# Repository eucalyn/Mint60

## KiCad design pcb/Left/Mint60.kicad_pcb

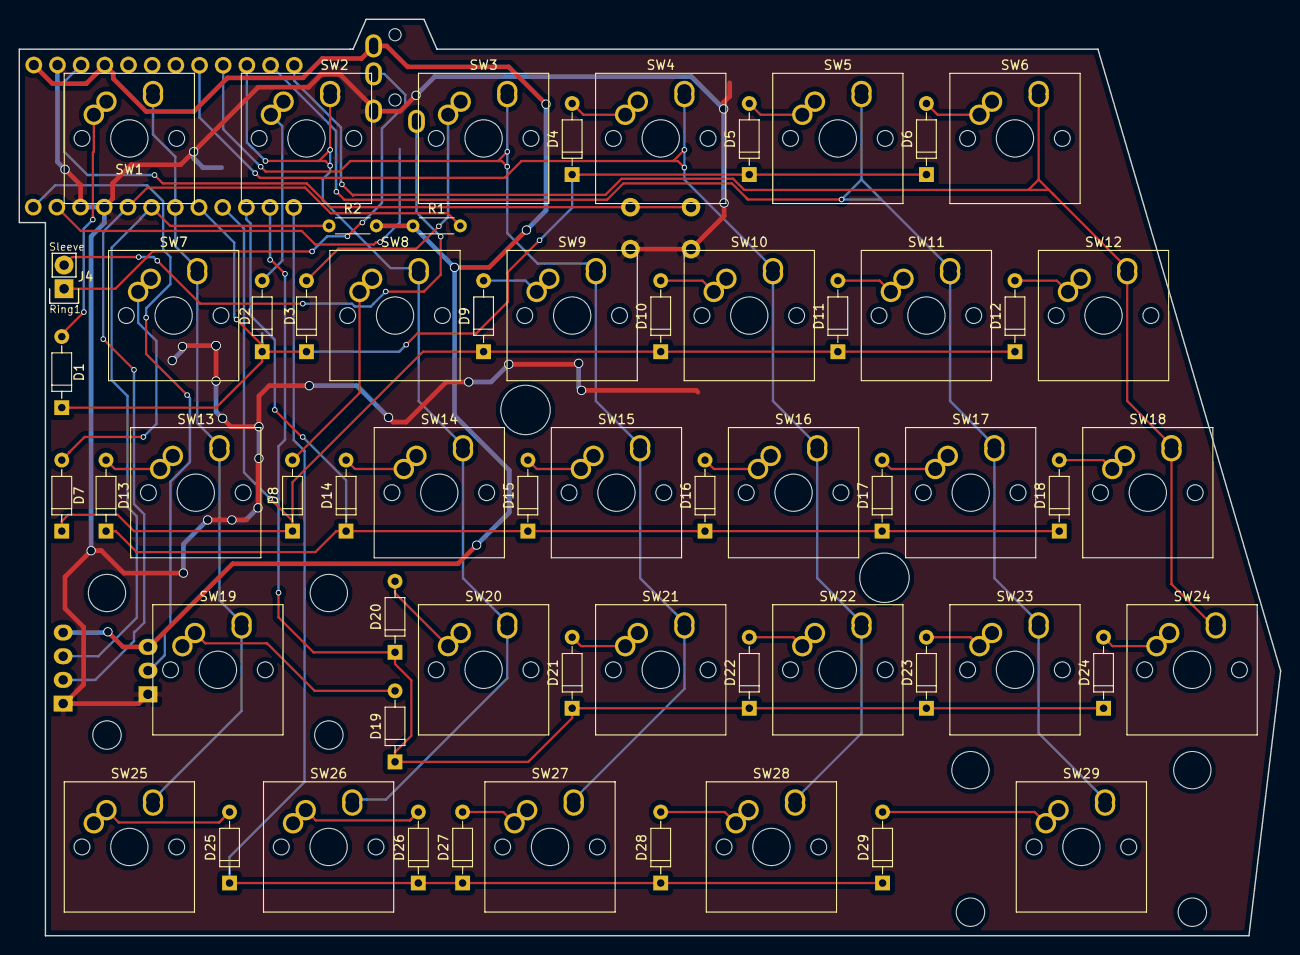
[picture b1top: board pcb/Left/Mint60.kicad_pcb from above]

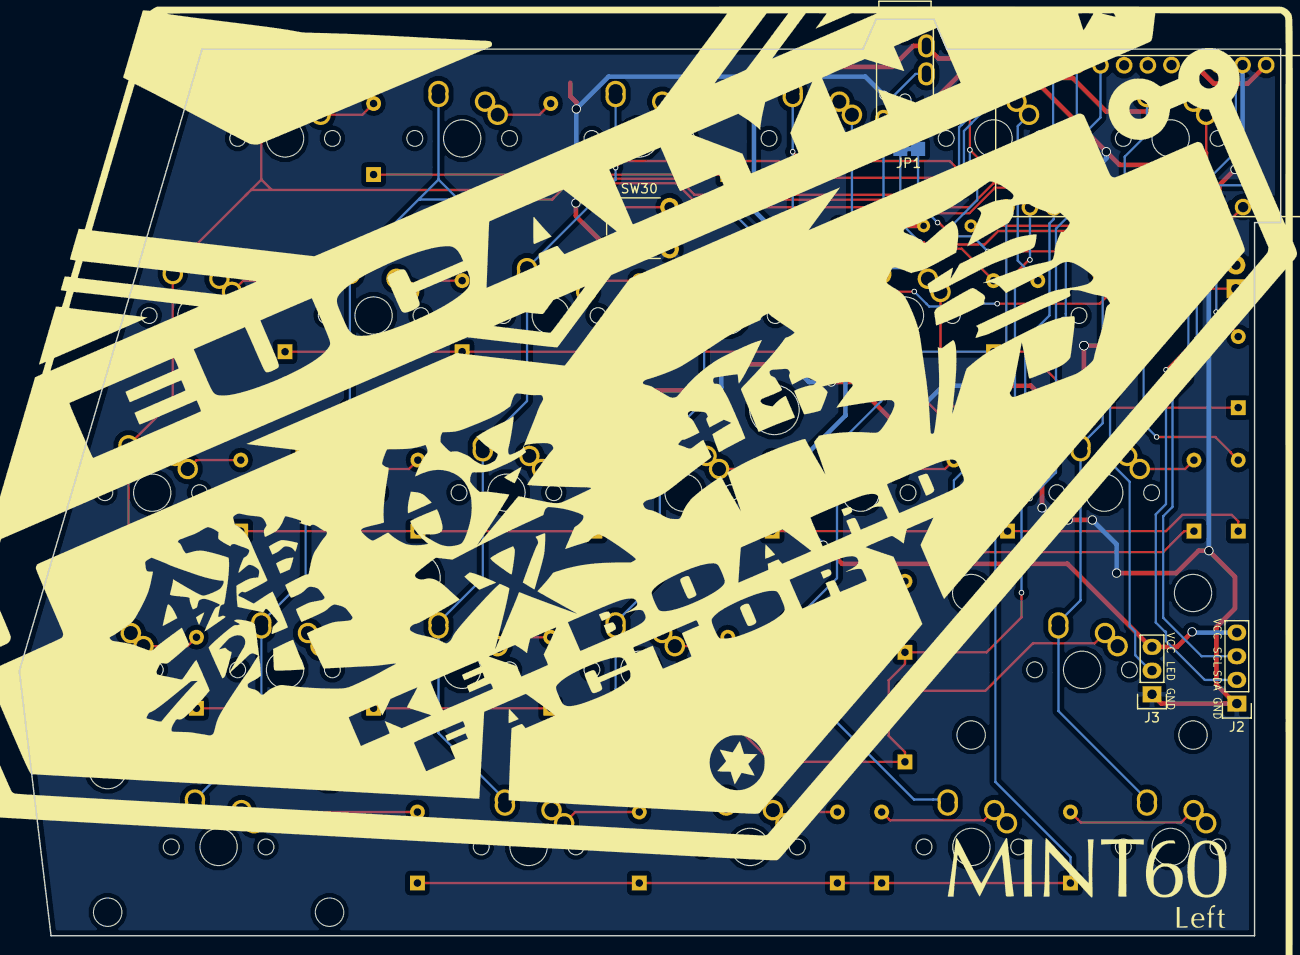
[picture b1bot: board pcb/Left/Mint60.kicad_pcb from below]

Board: 2 copper layers, 135.3 x 98.3 mm, 67 parts (5 on the bottom side), 49 nets.

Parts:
D1, D2, D3, D4, D5, D6, D7, D8, D9, D10, D11, D12, D13, D14, D15, D16, D17, D18, D19, D20, D21, D22, D23, D24, D25, D26, D27, D28, D29: D; Diode
J1: MJ-4PP-9; TRRS_JACK_MJ4PP9_fr
J2: Conn_01x04; Pin_Header_Straight_1x04
J3: Conn_01x03; Pin_Header_Straight_1x03
J4: Conn_01x02; Pin_Header_Straight_1x02
JP1: Jumper_NC_Small; JumperClose
R1, R2: R; R_Axial_DIN0204_L3.6mm_D1.6mm_P5.08mm_Horizontal
SW1, SW2, SW3, SW4, SW5, SW6, SW7, SW8, SW9, SW10, SW11, SW12, SW13, SW14, SW15, SW16, SW17, SW18, SW20, SW21, SW22, SW23, SW24, SW25, SW26, SW27, SW28: SW_Push; SW_Cherry_Matias_1.00u_PCB
SW19, SW29: SW_Push; SW_Cherry_Matias_2.00u_PCB-flip
SW30: SW_Push; SW_PUSH_6mm
U1: ProMicro; ProMicro-Flip

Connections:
+5V: J1.3, J2.4, J3.3, R1.1, R2.2, U1.21, U1.24
Col0: SW1.1, SW7.1, SW13.1, SW19.1, SW25.1, U1.7
Col1: SW2.1, SW8.1, SW14.1, SW20.1, SW26.1, U1.15
Col2: SW3.1, SW9.1, SW15.1, SW21.1, SW27.1, U1.16
Col3: SW4.1, SW10.1, SW16.1, SW22.1, SW28.1, U1.17
Col4: SW5.1, SW11.1, SW17.1, SW23.1, SW29.1, U1.14
Col5: SW6.1, SW12.1, SW18.1, SW24.1, U1.13
Data: JP1.1, U1.2
GND: J1.1, J2.1, J3.1, SW30.2, U1.3, U1.4, U1.23
LED: J3.2, U1.1
unnamed: D1.2, SW1.2
unnamed: D2.2, SW2.2
unnamed: D3.2, SW3.2
unnamed: D4.2, SW4.2
unnamed: D5.2, SW5.2
unnamed: D6.2, SW6.2
unnamed: D7.2, SW7.2
unnamed: D8.2, SW8.2
unnamed: D9.2, SW9.2
unnamed: D10.2, SW10.2
unnamed: D11.2, SW11.2
unnamed: D12.2, SW12.2
unnamed: D13.2, SW13.2
unnamed: D14.2, SW14.2
unnamed: D15.2, SW15.2
unnamed: D16.2, SW16.2
unnamed: D17.2, SW17.2
unnamed: D18.2, SW18.2
unnamed: D19.2, SW19.2
unnamed: D20.2, SW20.2
unnamed: D21.2, SW21.2
unnamed: D22.2, SW22.2
unnamed: D23.2, SW23.2
unnamed: D24.2, SW24.2
unnamed: D25.2, SW25.2
unnamed: D26.2, SW26.2
unnamed: D27.2, SW27.2
unnamed: D28.2, SW28.2
unnamed: D29.2, SW29.2
unnamed: J1.2, J4.1, JP1.2
unnamed: J1.4, J4.2
Reset: SW30.1, U1.22
Row0: D1.1, D2.1, D3.1, D4.1, D5.1, D6.1, U1.8
Row1: D7.1, D8.1, D9.1, D10.1, D11.1, D12.1, U1.9
Row2: D13.1, D14.1, D15.1, D16.1, D17.1, D18.1, U1.10
Row3: D19.1, D20.1, D21.1, D22.1, D23.1, D24.1, U1.11
Row4: D25.1, D26.1, D27.1, D28.1, D29.1, U1.12
SCL: J2.3, R2.1, U1.6
SDA: J2.2, R1.2, U1.5

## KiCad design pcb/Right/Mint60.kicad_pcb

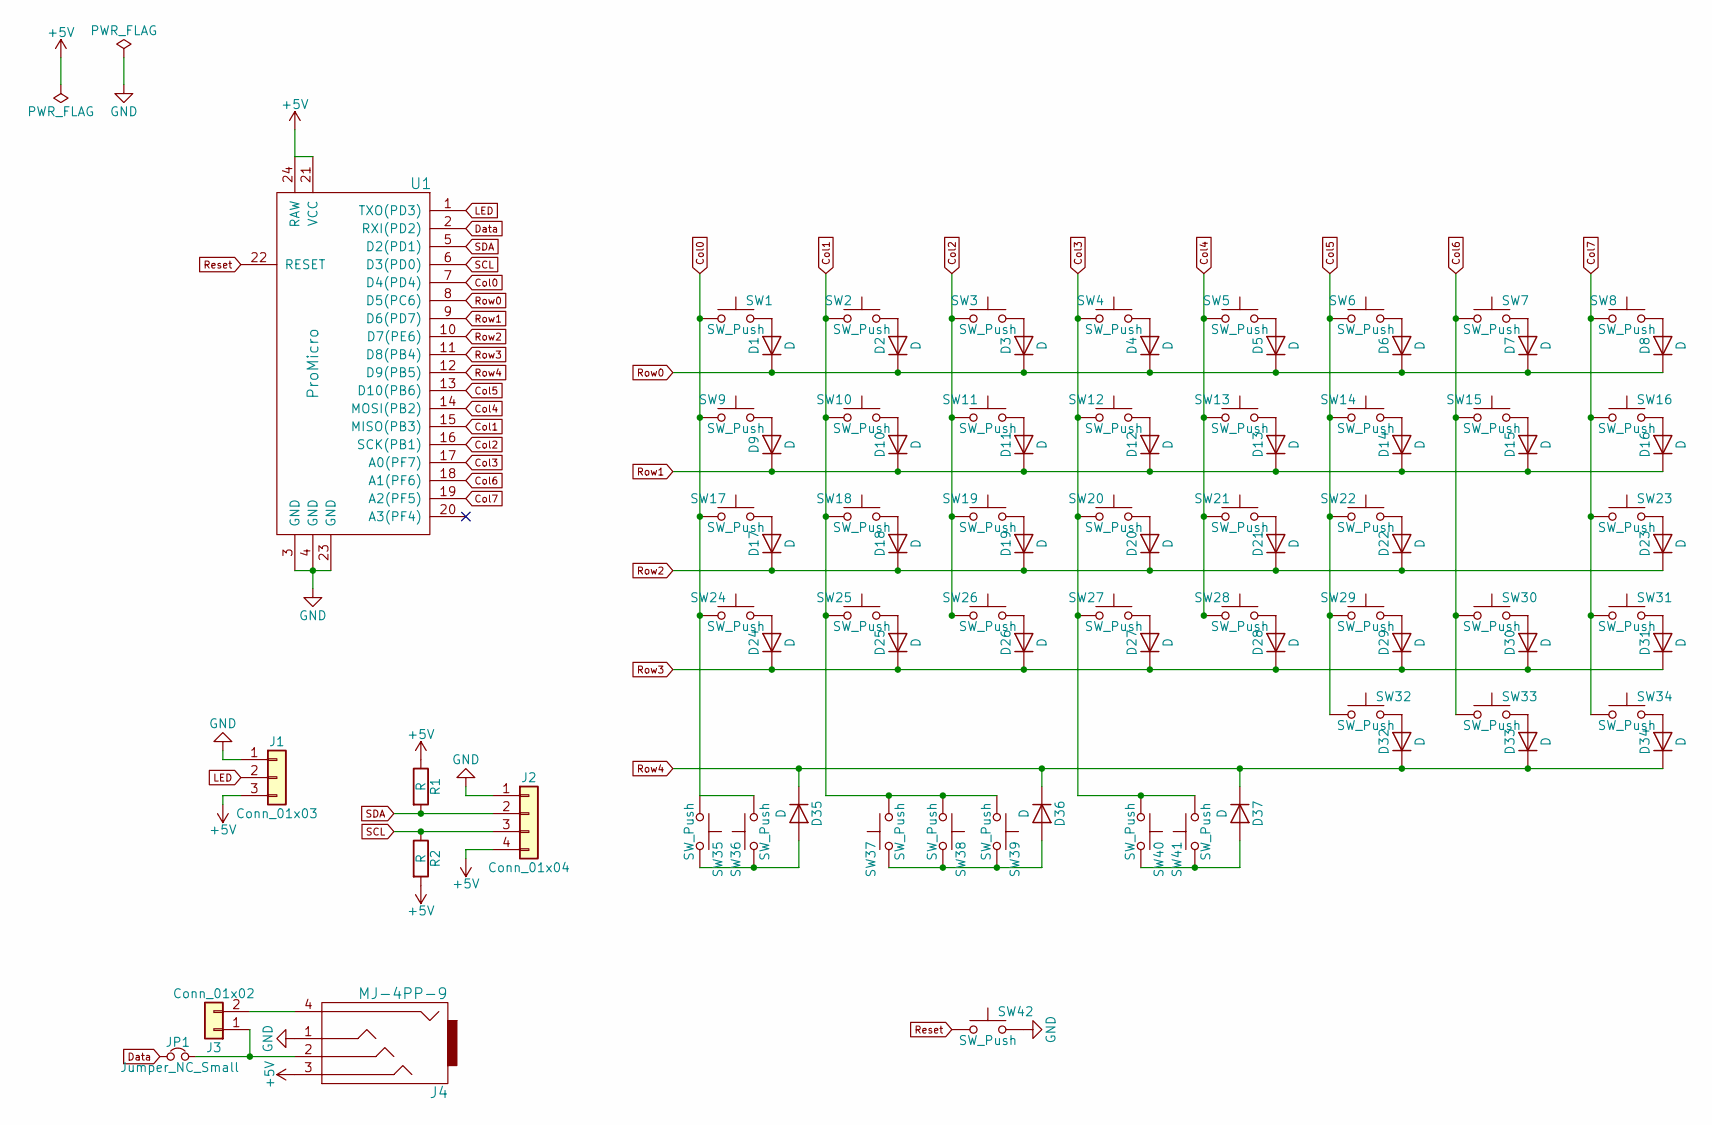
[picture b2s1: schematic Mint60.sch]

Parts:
D1, D2, D3, D4, D5, D6, D7, D8, D9, D10, D11, D12, D13, D14, D15, D16, D17, D18, D19, D20, D21, D22, D23, D24, D25, D26, D27, D28, D29, D30, D31, D32, D33, D34, D35, D36, D37: D; Diode
J1: Conn_01x03; Pin_Header_Straight_1x03
J2: Conn_01x04; Pin_Header_Straight_1x04
J3: Conn_01x02; Pin_Header_Straight_1x02
J4: MJ-4PP-9; TRRS_JACK_MJ4PP9_fr
JP1: Jumper_NC_Small; JumperClose
R1, R2: R; R_Axial_DIN0204_L3.6mm_D1.6mm_P5.08mm_Horizontal
SW1, SW2, SW3, SW4, SW5, SW6, SW7, SW9, SW10, SW11, SW12, SW13, SW14, SW15, SW16, SW17, SW18, SW19, SW20, SW21, SW22, SW24, SW25, SW26, SW27, SW28, SW29, SW30, SW31, SW32, SW33, SW34, SW35, SW37, SW38, SW39, SW41: SW_Push; SW_Cherry_Matias_1.00u_PCB
SW8: SW_Push; SW_Cherry_Matias_2.00u_PCB
SW23, SW36, SW40: SW_Push; SW_Cherry_Matias_2.00u_PCB-flip
SW42: SW_Push; SW_PUSH_6mm
U1: ProMicro; ProMicro-Flip

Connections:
+5V: J1.3, J2.4, J4.3, R1.1, R2.2, U1.21 (VCC), U1.24 (RAW)
Col0: SW1.1, SW9.2, SW17.2, SW24.2, SW35.1, SW36.1, U1.7 (D4(PD4))
Col1: SW2.2, SW10.2, SW18.2, SW25.2, SW37.1, SW38.1, SW39.1, U1.15 (MISO(PB3))
Col2: SW3.2, SW11.2, SW19.2, SW26.2, U1.16 (SCK(PB1))
Col3: SW4.2, SW12.2, SW20.2, SW27.2, SW40.1, SW41.1, U1.17 (A0(PF7))
Col4: SW5.2, SW13.2, SW21.2, SW28.2, U1.14 (MOSI(PB2))
Col5: SW6.2, SW14.2, SW22.2, SW29.2, SW32.1, U1.13 (D10(PB6))
Col6: SW7.1, SW15.2, SW30.1, SW33.1, U1.18 (A1(PF6))
Col7: SW8.2, SW16.1, SW23.1, SW31.1, SW34.1, U1.19 (A2(PF5))
Data: JP1.1, U1.2 (RXI(PD2))
GND: J1.1, J2.1, J4.1, SW42.2, U1.3 (GND), U1.4 (GND), U1.23 (GND)
LED: J1.2, U1.1 (TXO(PD3))
unnamed: D1.2 (A), SW1.2
unnamed: D2.2 (A), SW2.1
unnamed: D3.2 (A), SW3.1
unnamed: D4.2 (A), SW4.1
unnamed: D5.2 (A), SW5.1
unnamed: D6.2 (A), SW6.1
unnamed: D7.2 (A), SW7.2
unnamed: D8.2 (A), SW8.1
unnamed: D9.2 (A), SW9.1
unnamed: D10.2 (A), SW10.1
unnamed: D11.2 (A), SW11.1
unnamed: D12.2 (A), SW12.1
unnamed: D13.2 (A), SW13.1
unnamed: D14.2 (A), SW14.1
unnamed: D15.2 (A), SW15.1
unnamed: D16.2 (A), SW16.2
unnamed: D17.2 (A), SW17.1
unnamed: D18.2 (A), SW18.1
unnamed: D19.2 (A), SW19.1
unnamed: D20.2 (A), SW20.1
unnamed: D21.2 (A), SW21.1
unnamed: D22.2 (A), SW22.1
unnamed: D23.2 (A), SW23.2
unnamed: D24.2 (A), SW24.1
unnamed: D25.2 (A), SW25.1
unnamed: D26.2 (A), SW26.1
unnamed: D27.2 (A), SW27.1
unnamed: D28.2 (A), SW28.1
unnamed: D29.2 (A), SW29.1
unnamed: D30.2 (A), SW30.2
unnamed: D31.2 (A), SW31.2
unnamed: D32.2 (A), SW32.2
unnamed: D33.2 (A), SW33.2
unnamed: D34.2 (A), SW34.2
unnamed: D35.2 (A), SW35.2, SW36.2
unnamed: D36.2 (A), SW37.2, SW38.2, SW39.2
unnamed: D37.2 (A), SW40.2, SW41.2
unnamed: J3.1, J4.2, JP1.2
unnamed: J3.2, J4.4
Reset: SW42.1, U1.22 (RESET)
Row0: D1.1 (K), D2.1 (K), D3.1 (K), D4.1 (K), D5.1 (K), D6.1 (K), D7.1 (K), D8.1 (K), U1.8 (D5(PC6))
Row1: D9.1 (K), D10.1 (K), D11.1 (K), D12.1 (K), D13.1 (K), D14.1 (K), D15.1 (K), D16.1 (K), U1.9 (D6(PD7))
Row2: D17.1 (K), D18.1 (K), D19.1 (K), D20.1 (K), D21.1 (K), D22.1 (K), D23.1 (K), U1.10 (D7(PE6))
Row3: D24.1 (K), D25.1 (K), D26.1 (K), D27.1 (K), D28.1 (K), D29.1 (K), D30.1 (K), D31.1 (K), U1.11 (D8(PB4))
Row4: D32.1 (K), D33.1 (K), D34.1 (K), D35.1 (K), D36.1 (K), D37.1 (K), U1.12 (D9(PB5))
SCL: J2.3, R2.1, U1.6 (D3(PD0))
SDA: J2.2, R1.2, U1.5 (D2(PD1))

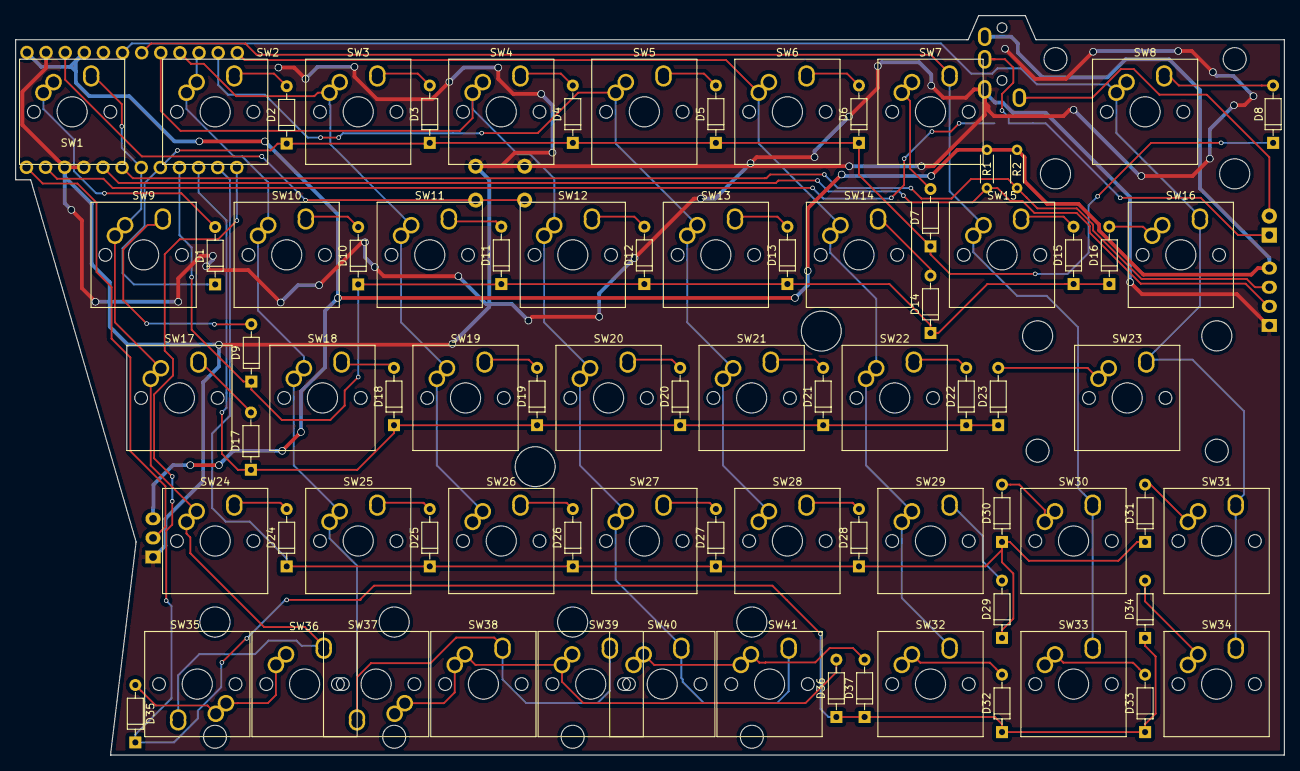
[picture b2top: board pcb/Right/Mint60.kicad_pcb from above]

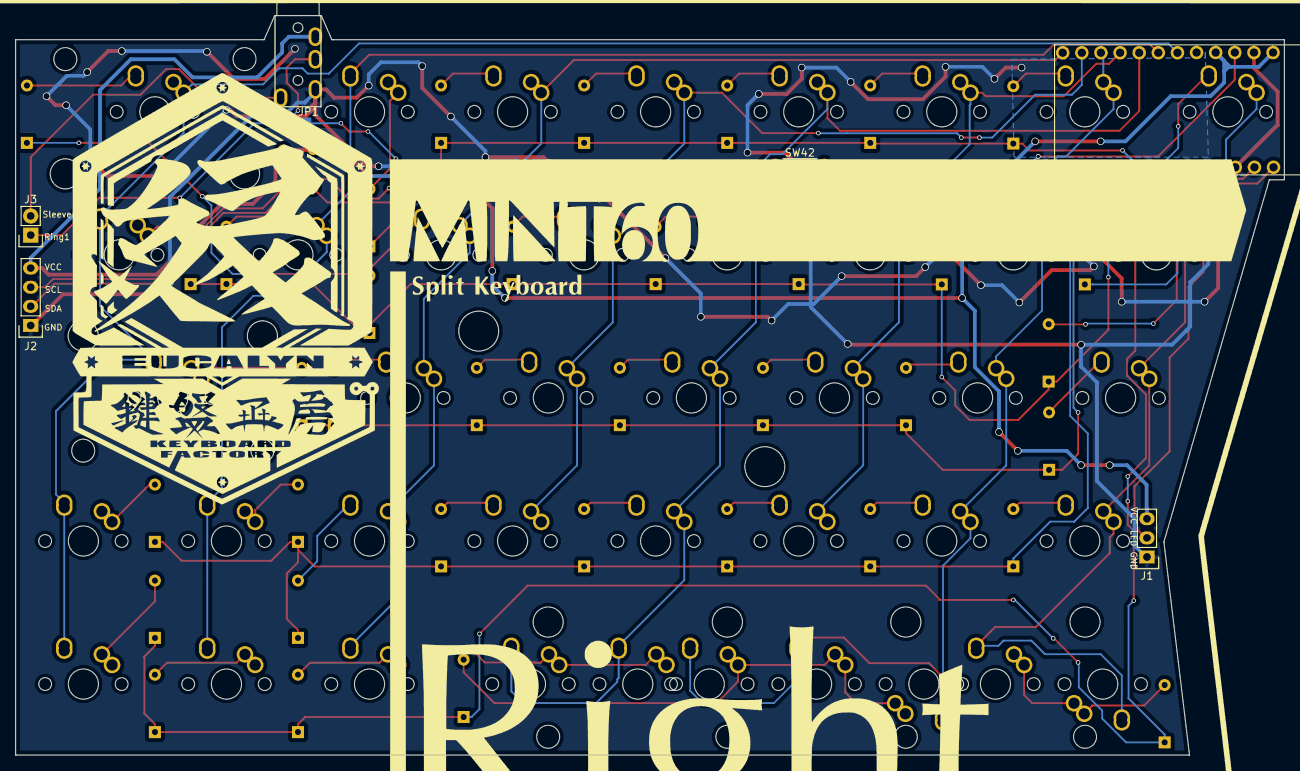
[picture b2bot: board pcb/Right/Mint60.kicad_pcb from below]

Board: 2 copper layers, 168.5 x 98.2 mm, 87 parts (6 on the bottom side), 59 nets.

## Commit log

2018-10-14 add Files
2018-10-14 add gitignore
2018-10-14 del DS_Store
2018-10-14 del DS_Stores
2019-04-20 added default keyboard layout image and json file
2019-04-20 modifed image url
2019-04-20 modifed json url
2019-04-20 modifed json url (to raw file)
